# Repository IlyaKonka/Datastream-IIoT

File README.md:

# Data Stream Processing in IIoT environments
## Video demonstration

## Video description
At the top of the video you can see log output of IIoT-System.
There is vibration visualisation in the right corner and live video of the lego prototype in the left corner.<br>
<br>
<br>
Timecodes:
* (0:00 — 0:30) start of IIoT-System
* (0:30 — 0:52) response of **identification module** to the lego part without id tag 
* (0:54 — 2:53) production workflow of **defect 1** lego part 
* (1:30 — 1:45) demonstration of predictive maintenance
* (2:56 — 4:40) production workflow of **non-defective** lego part
* (4:45 — 5:00) transport to the **drop zone** the lego part which has already been processed

## Sensor simulators
You can start the docker project with vibration/color sensor simulator(s).
There is more information in the **IIoT-System** folder.

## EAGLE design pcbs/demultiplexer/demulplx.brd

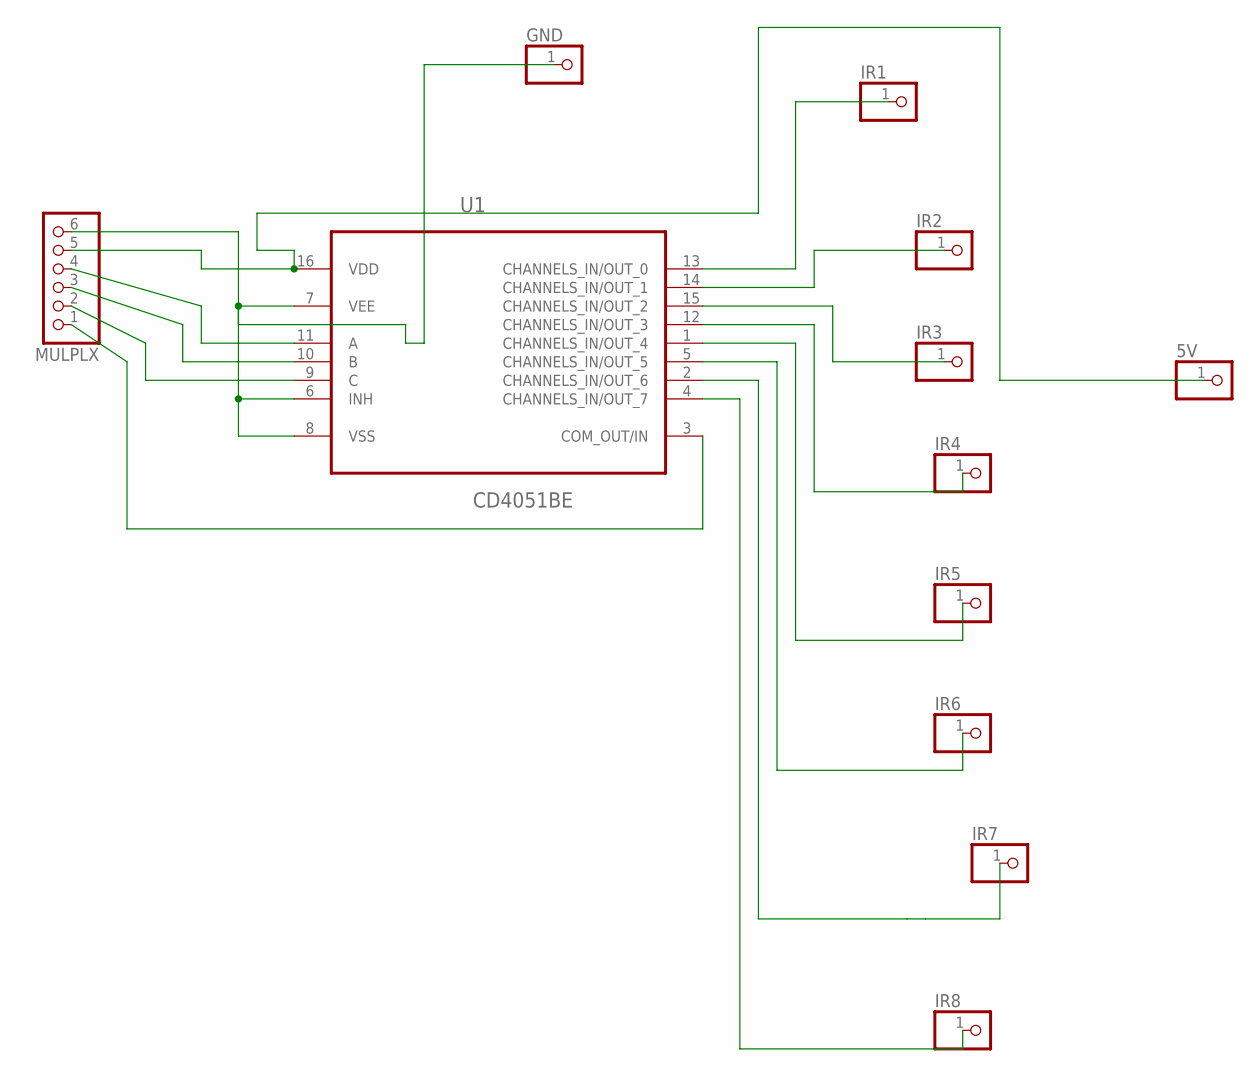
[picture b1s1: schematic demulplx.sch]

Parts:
5V: PINHD-1X01_2.54; 1X01
GND: PINHD-1X01_2.54; 1X01
IR1, IR2, IR3, IR4, IR5, IR6, IR7, IR8: PINHD-1X01_2.54; 1X01
MULPLX: PINHD-1X06_2.54-S; 1X06-S
U1: CD4051BE; DIP254P762X508-16

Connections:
5V: 5V.1, MULPLX.5, U1.16 (VDD)
GND: GND.1, MULPLX.6, U1.6 (INH), U1.7 (VEE), U1.8 (VSS)
unnamed: IR7.1, U1.2 (CHANNELS_IN/OUT_6)
unnamed: IR1.1, U1.13 (CHANNELS_IN/OUT_0)
unnamed: IR2.1, U1.14 (CHANNELS_IN/OUT_1)
unnamed: IR3.1, U1.15 (CHANNELS_IN/OUT_2)
unnamed: IR4.1, U1.12 (CHANNELS_IN/OUT_3)
unnamed: IR5.1, U1.1 (CHANNELS_IN/OUT_4)
unnamed: IR6.1, U1.5 (CHANNELS_IN/OUT_5)
unnamed: IR8.1, U1.4 (CHANNELS_IN/OUT_7)
unnamed: MULPLX.1, U1.3 (COM_OUT/IN)
unnamed: MULPLX.4, U1.11 (A)
unnamed: MULPLX.3, U1.10 (B)
unnamed: MULPLX.2, U1.9 (C)

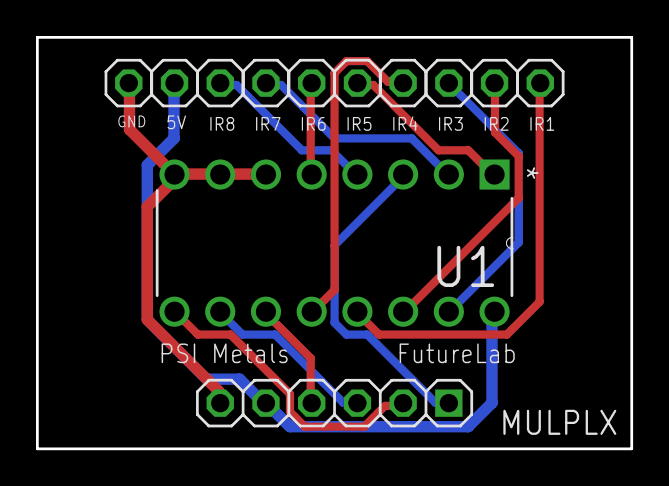
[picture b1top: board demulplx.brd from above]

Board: 2 copper layers, 33.0 x 22.9 mm, 12 parts (0 on the bottom side), 14 nets.

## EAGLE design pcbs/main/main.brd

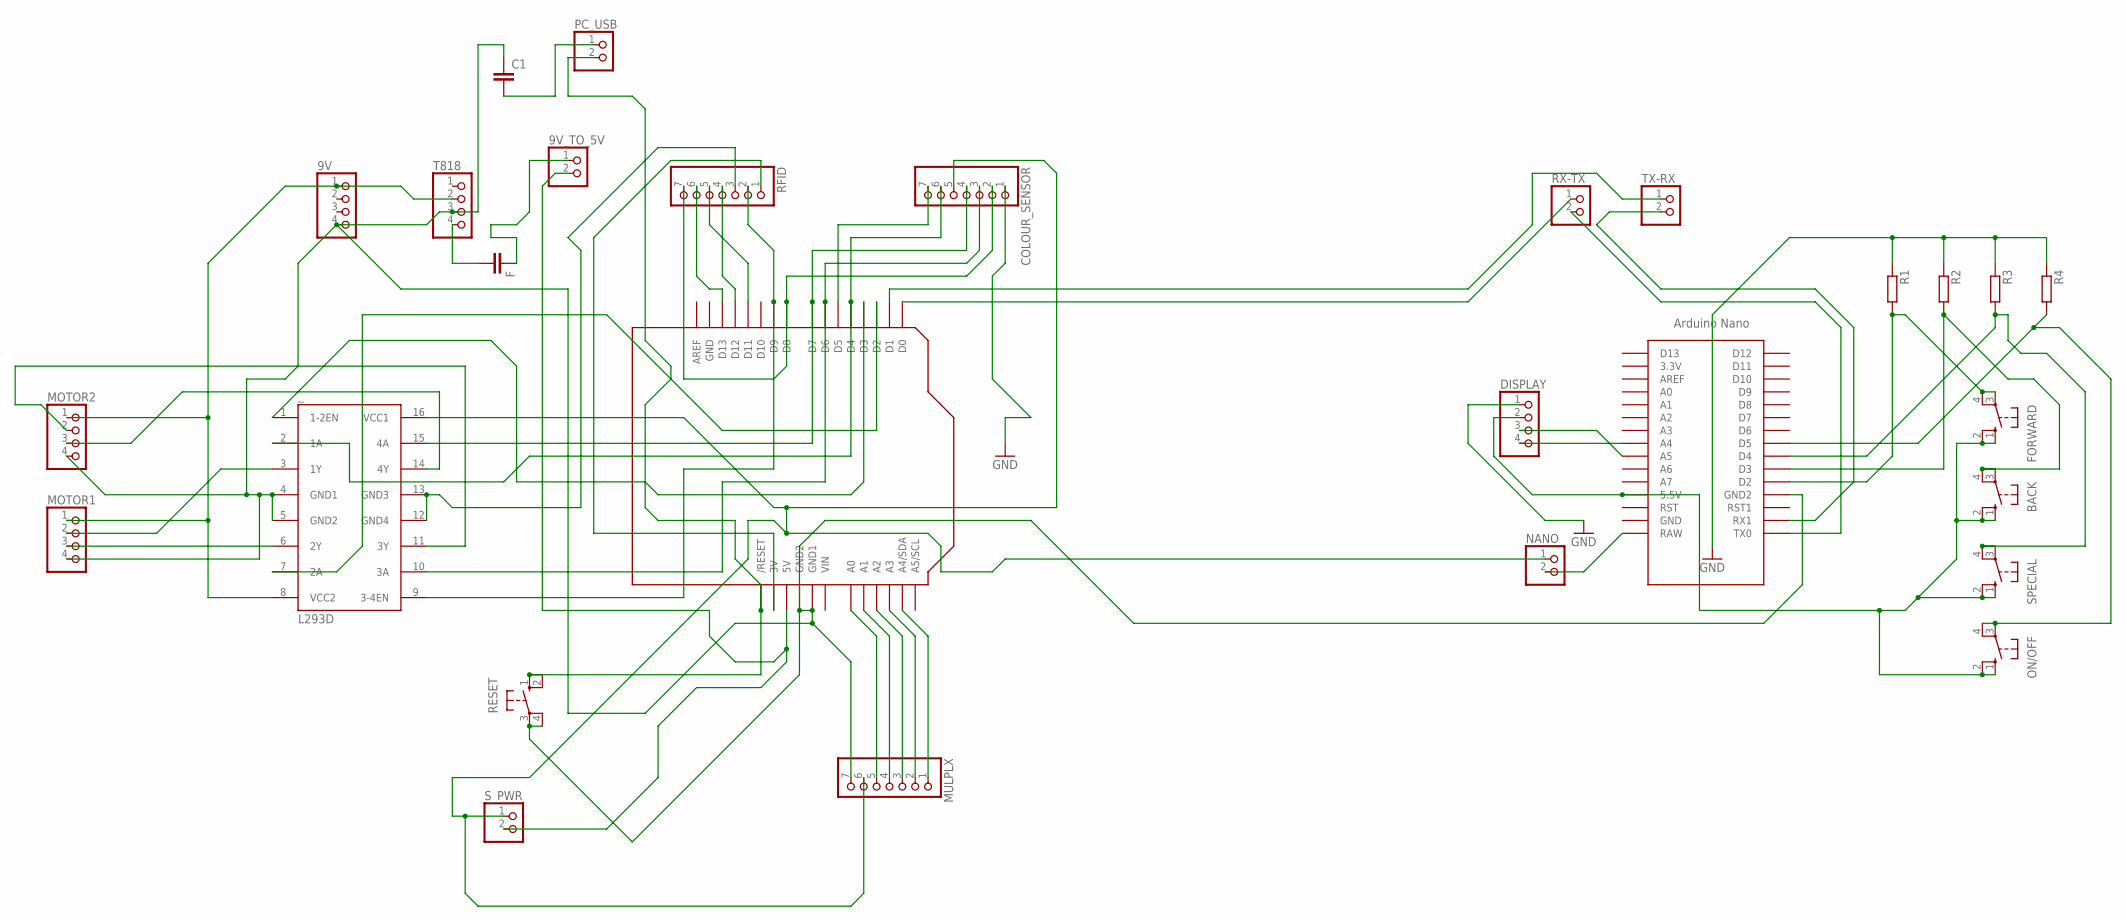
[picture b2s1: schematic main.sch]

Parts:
9V: PINHD-1X04_2.54-S; 1X04-S
9V_TO_5V: PINHD-1X02_2.54-S; 1X02-S
BACK: 10-XX; B3F-10XX
C1: C5/7.2; C5B7.2
COLOUR_SENSOR: PINHD-1X07_2.54-S; 1X07-S
DISPLAY: PINHD-1X04_2.54-S; 1X04-S
F: CC4532; C4532
FORWARD: 10-XX; B3F-10XX
MOTOR1, MOTOR2: PINHD-1X04_2.54-S; 1X04-S
MULPLX: PINHD-1X07_2.54-S; 1X07-S
NANO: PINHD-1X02_2.54-S; 1X02-S
ON/OFF: 10-XX; B3F-10XX
PC_USB: PINHD-1X02_2.54-S; 1X02-S
R1, R2, R3, R4: R-EU_R0805; R0805
RESET: 10-XX; B3F-10XX
RFID: PINHD-1X07_2.54-S; 1X07-S
RX-TX: PINHD-1X02_2.54-S; 1X02-S
SPECIAL: 10-XX; B3F-10XX
S_PWR: PINHD-1X02_2.54-S; 1X02-S
T818: PINHD-1X04_2.54-S; 1X04-S
TX-RX: PINHD-1X02_2.54-S; 1X02-S
U1: ARDUINOR3-DIMENSION; ARDUINOR3
U$1: NANO
_: L293D; DIL16

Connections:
GND: 9V.4, C1.1, COLOUR_SENSOR.1, DISPLAY.1, MOTOR1.4, MOTOR2.4, MULPLX.7, R1.1, R2.1, R3.1, R4.1, RESET.3, RESET.4 (P1), T818.3, U1.GND, U1.GND1, U1.GND2, U$1.GND1 (GND2), _.4 (GND1), _.5 (GND2)
unnamed: RFID.3, _.12 (GND4), _.13 (GND3)
unnamed: F.2, T818.4
unnamed: 9V_TO_5V.2, S_PWR.2, U1.5V
unnamed: COLOUR_SENSOR.2, RFID.7, U1.D8
unnamed: MULPLX.1, U1.A4 (A4/SDA)
unnamed: MULPLX.5, U1.A0
unnamed: MULPLX.4, U1.A1
unnamed: MULPLX.3, U1.A2
unnamed: MULPLX.2, U1.A3
unnamed: ON/OFF.3, ON/OFF.4 (P1), R4.2, U$1.D5
unnamed: COLOUR_SENSOR.7, U1.D5
unnamed: BACK.1 (S), BACK.2 (S1), DISPLAY.2, FORWARD.1 (S), FORWARD.2 (S1), ON/OFF.1 (S), ON/OFF.2 (S1), SPECIAL.1 (S), SPECIAL.2 (S1), U$1.5V (5.5V)
unnamed: PC_USB.2, RESET.1 (S), RESET.2 (S1), U1.RESET (/RESET)
unnamed: DISPLAY.3, U$1.A5
unnamed: DISPLAY.4, U$1.A4
unnamed: C1.2, PC_USB.1
unnamed: COLOUR_SENSOR.6, U1.D4, _.2 (1A)
unnamed: 9V.1, MOTOR1.1, MOTOR2.1, T818.2, _.8 (VCC2)
unnamed: RFID.1, U1.3V
unnamed: FORWARD.3, FORWARD.4 (P1), R1.2, U$1.D2
unnamed: RX-TX.1, U1.D0
unnamed: RX-TX.2, U$1.TX0
unnamed: TX-RX.1, U1.D1
unnamed: TX-RX.2, U$1.RX1
unnamed: NANO.2, U$1.RAW
unnamed: BACK.3, BACK.4 (P1), R2.2, U$1.D3
unnamed: RFID.2, U1.D9, _.9 (3-4EN)
unnamed: R3.2, SPECIAL.3, SPECIAL.4 (P1), U$1.D4
unnamed: 9V_TO_5V.1, F.1
unnamed: COLOUR_SENSOR.3, U1.D6, _.10 (3A)
unnamed: COLOUR_SENSOR.4, U1.D7, _.15 (4A)
unnamed: RFID.4, U1.D12
unnamed: RFID.5, U1.D11
unnamed: RFID.6, U1.D13
unnamed: COLOUR_SENSOR.5, MULPLX.6, NANO.1, S_PWR.1, _.16 (VCC1)
unnamed: MOTOR1.2, _.3 (1Y)
unnamed: MOTOR1.3, _.6 (2Y)
unnamed: MOTOR2.2, _.11 (3Y)
unnamed: MOTOR2.3, _.14 (4Y)
unnamed: U1.D3, _.1 (1-2EN)
unnamed: U1.D2, _.7 (2A)
VIN: U1.VIN

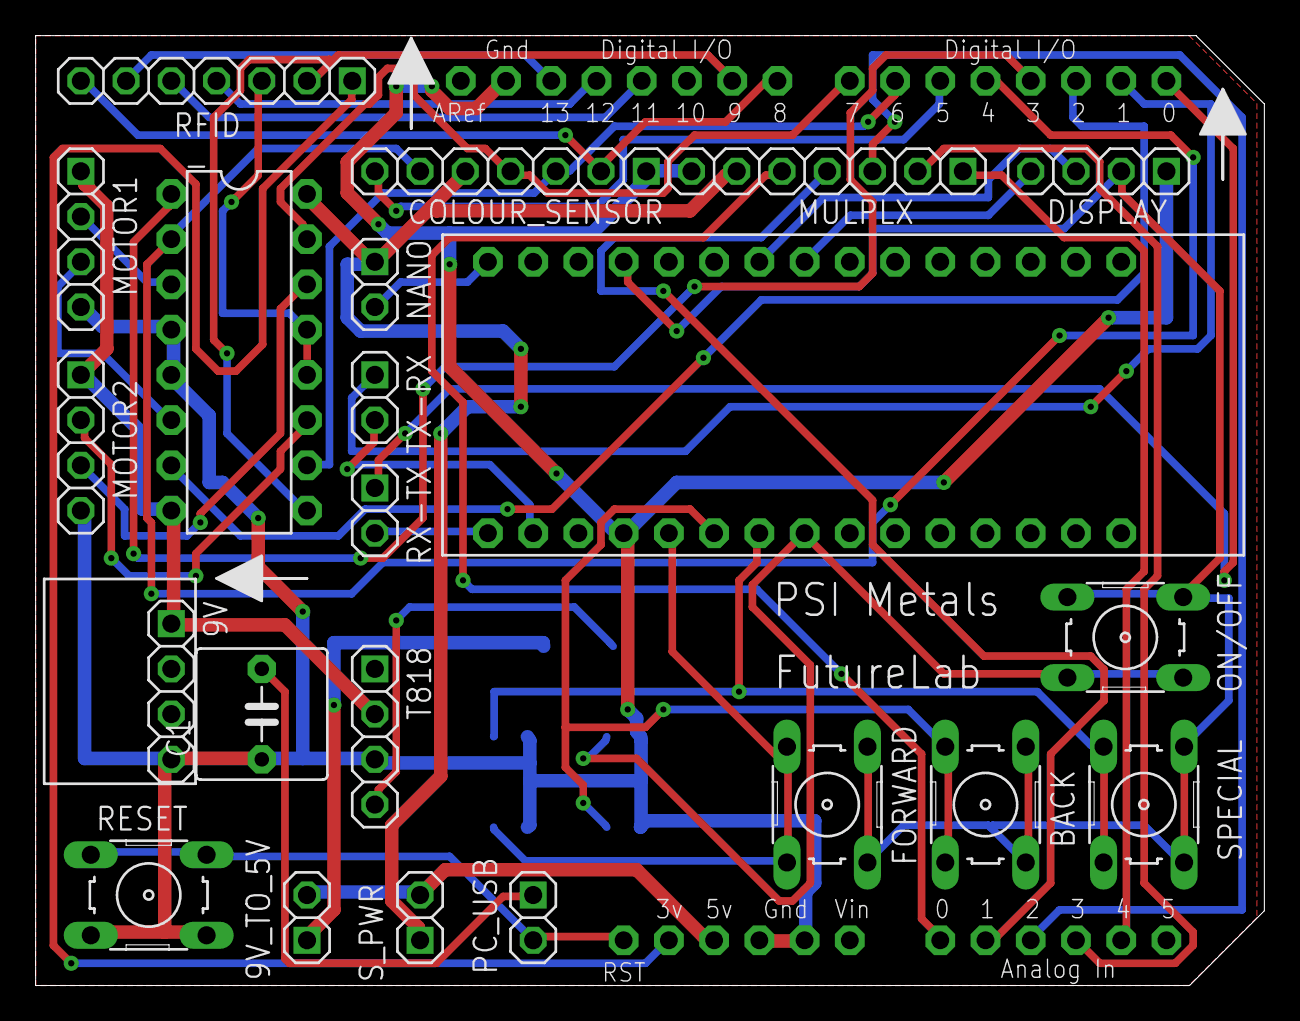
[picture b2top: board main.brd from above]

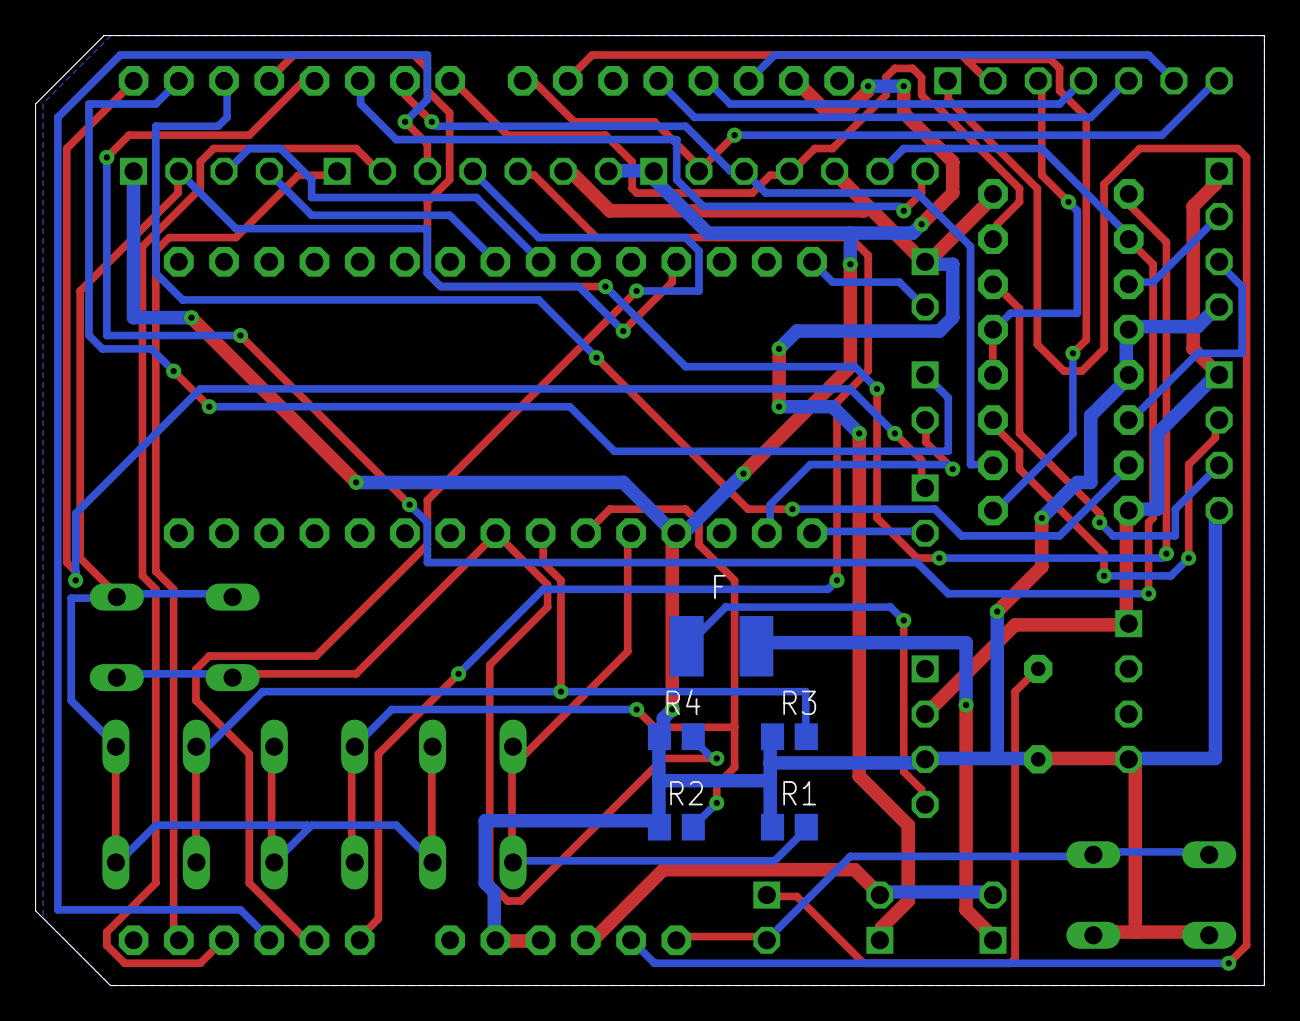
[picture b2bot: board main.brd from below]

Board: 2 copper layers, 69.0 x 53.3 mm, 28 parts (5 on the bottom side), 42 nets.

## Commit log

2021-04-10 init commit
